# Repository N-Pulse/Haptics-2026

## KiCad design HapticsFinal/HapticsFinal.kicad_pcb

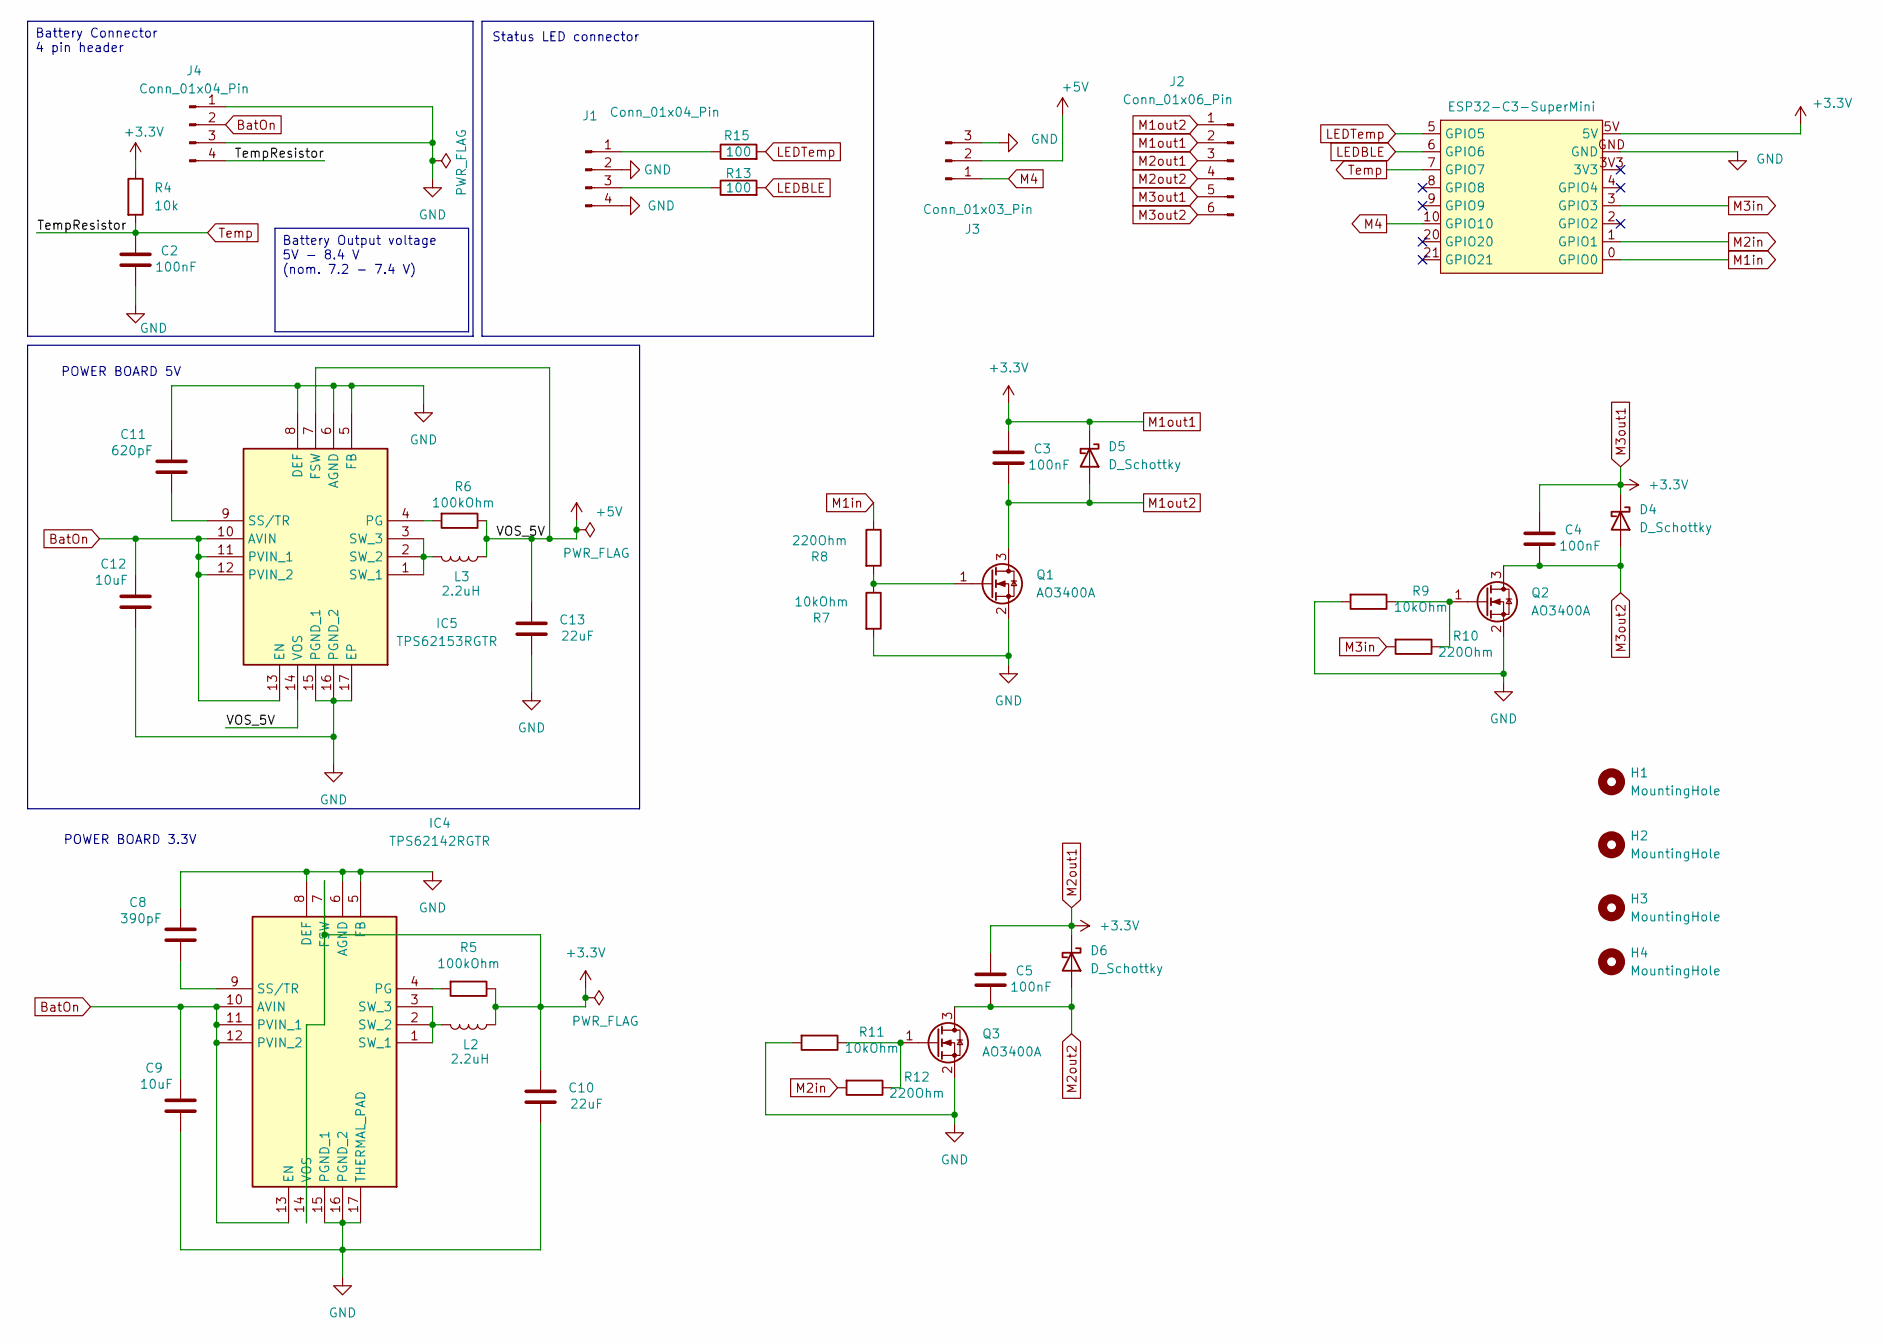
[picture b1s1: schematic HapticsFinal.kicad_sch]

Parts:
C2, C3, C4, C5: 100nF; C_1206_3216Metric_Pad1.33x1.80mm_HandSolder
C8: 390pF; C_0603_1608Metric_Pad1.08x0.95mm_HandSolder
C9, C12: 10uF; C_0603_1608Metric_Pad1.08x0.95mm_HandSolder
C10, C13: 22uF; C_1210_3225Metric_Pad1.33x2.70mm_HandSolder
C11: 620pF; C_0603_1608Metric_Pad1.08x0.95mm_HandSolder
D4, D5, D6: D_Schottky; D_SOD-123F
H1, H2, H3, H4: MountingHole; MountingHole_2.2mm_M2
IC4: TPS62142RGTR; QFN50P300X300X100-17N-D; Manufacturer_Part_Number TPS62142RGTR; Mouser Part Number 595-TPS62142RGTR
IC5: TPS62153RGTR; QFN50P300X300X100-17N-D; Manufacturer_Part_Number TPS62153RGTR; Mouser Part Number 595-TPS62153RGTR
J1, J4: Conn_01x04_Pin; PinHeader_1x04_P1.00mm_Vertical
J2: Conn_01x06_Pin; PinHeader_1x06_P1.00mm_Vertical
J3: Conn_01x03_Pin; PinHeader_1x03_P1.00mm_Vertical
L2, L3: 2.2uH; 1269ASH100NP2
Q1, Q2, Q3: AO3400A; SOT-23
R4: 10k; R_0603_1608Metric_Pad0.98x0.95mm_HandSolder
R5, R6: 100kOhm; R_0603_1608Metric_Pad0.98x0.95mm_HandSolder
R7, R9, R11: 10kOhm; R_0603_1608Metric_Pad0.98x0.95mm_HandSolder
R8, R10, R12: 220Ohm; R_0603_1608Metric_Pad0.98x0.95mm_HandSolder
R13, R15: 100; R_0603_1608Metric_Pad0.98x0.95mm_HandSolder
U2: ESP32-C3-SuperMini

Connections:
+5V: C13.2, IC5.7 (FSW), IC5.14 (VOS), J3.2, L3.1, R6.1
BatOn: C9.1, C12.1, IC4.10 (AVIN), IC4.11 (PVIN_1), IC4.12 (PVIN_2), IC4.13 (EN), IC5.10 (AVIN), IC5.11 (PVIN_1), IC5.12 (PVIN_2), IC5.13 (EN), J4.2
GND: C2.2, C8.1, C9.2, C10.1, C11.1, C12.2, C13.1, IC4.5 (FB), IC4.6 (AGND), IC4.8 (DEF), IC4.15 (PGND_1), IC4.16 (PGND_2), IC4.17 (THERMAL_PAD), IC5.5 (FB), IC5.6 (AGND), IC5.8 (DEF), IC5.15 (PGND_1), IC5.16 (PGND_2), IC5.17 (EP), J1.2, J1.4, J3.3, J4.1, J4.3, Q1.2 (S), Q2.2 (S), Q3.2 (S), R7.2, R9.2, R11.2, U2.GND
LEDBLE: R13.2, U2.6 (GPIO6)
LEDTemp: R15.2, U2.5 (GPIO5)
M1in: R8.1, U2.0 (GPIO0)
M1out1: C3.1, C4.1, C5.1, C10.2, D4.1 (K), D5.1 (K), D6.1 (K), IC4.7 (FSW), IC4.14 (VOS), J2.2, J2.3, J2.5, L2.1, R4.1, R5.1, U2.5V
M1out2: C3.2, D5.2 (A), J2.1, Q1.3 (D)
M2in: R12.2, U2.1 (GPIO1)
M2out2: C5.2, D6.2 (A), J2.4, Q3.3 (D)
M3in: R10.2, U2.3 (GPIO3)
M3out2: C4.2, D4.2 (A), J2.6, Q2.3 (D)
M4: J3.1, U2.10 (GPIO10)
unnamed: IC4.4 (PG), R5.2
unnamed: C8.2, IC4.9 (SS/TR)
unnamed: IC4.1 (SW_1), IC4.2 (SW_2), IC4.3 (SW_3), L2.2
unnamed: IC5.4 (PG), R6.2
unnamed: C11.2, IC5.9 (SS/TR)
unnamed: IC5.1 (SW_1), IC5.2 (SW_2), IC5.3 (SW_3), L3.2
unnamed: J1.1, R15.1
unnamed: J1.3, R13.1
unnamed: Q1.1 (G), R7.1, R8.2
unnamed: Q2.1 (G), R9.1, R10.1
unnamed: Q3.1 (G), R11.1, R12.1
Temp: C2.1, J4.4, R4.2, U2.7 (GPIO7)

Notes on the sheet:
Status LED connector
POWER BOARD 3.3V
POWER BOARD 5V
Battery Connector 4 pin header
Battery Output voltage 5V - 8.4 V (nom. 7.2 - 7.4 V)

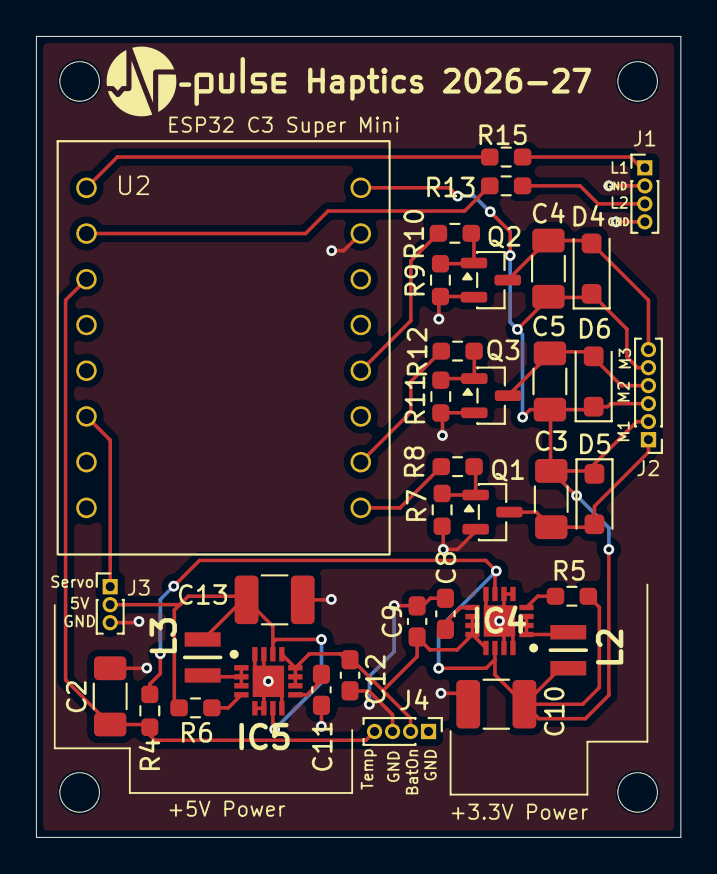
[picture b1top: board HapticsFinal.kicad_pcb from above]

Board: 2 copper layers, 35.8 x 44.5 mm, 40 parts (0 on the bottom side), 25 nets.
